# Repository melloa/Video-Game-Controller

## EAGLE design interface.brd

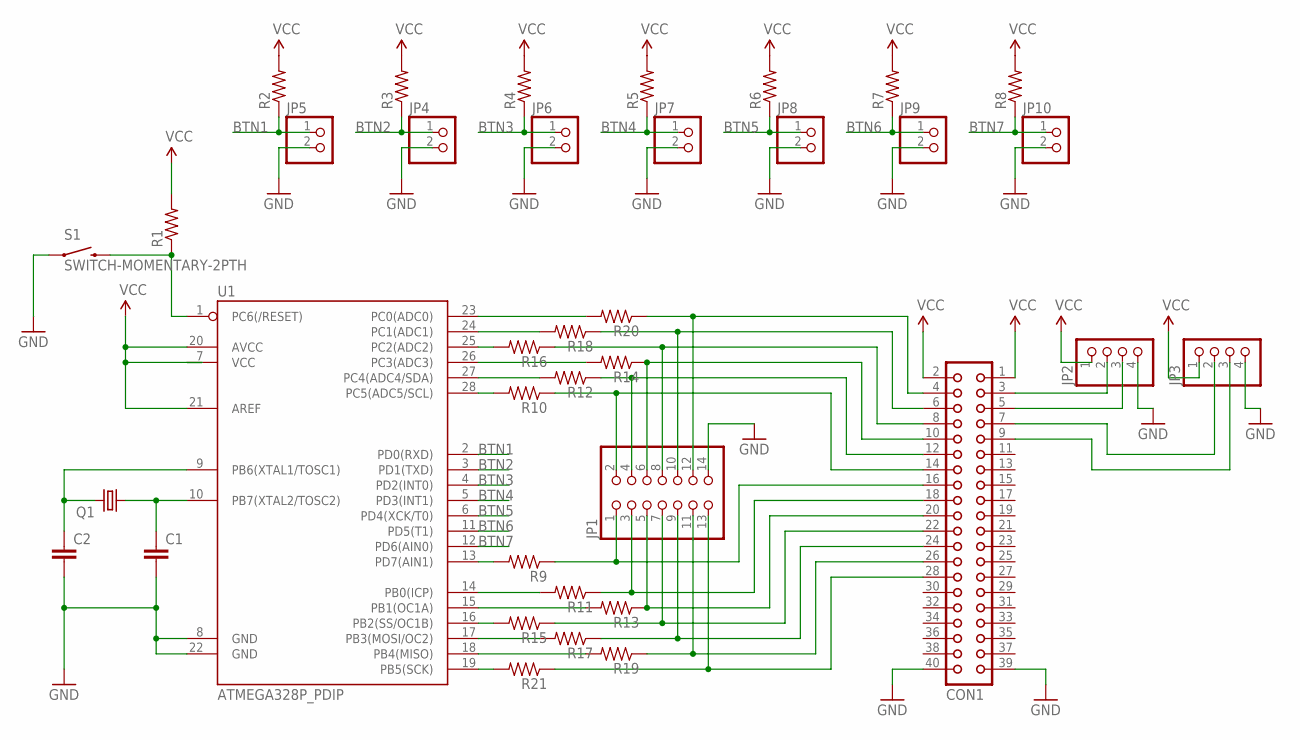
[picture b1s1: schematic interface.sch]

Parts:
C1, C2: CAPPTH; CAP-PTH-SMALL
CON1: CON40
JP1: PINHD-2X7; 2X07
JP2, JP3: PINHD-1X4; 1X04
JP4, JP5, JP6, JP7, JP8, JP9, JP10: PINHD-1X2; 1X02
Q1: CRYSTALHC49S; HC49/S
R1, R2, R3, R4, R5, R6, R7, R8, R9, R10, R11, R12, R13, R14, R15, R16, R17, R18, R19, R20, R21: RESISTORPTH-1/4W; AXIAL-0.4
S1: SWITCH-MOMENTARY-2PTH; TACTILE-PTH
U1: ATMEGA328P_PDIP; DIL28-3

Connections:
BTN1: JP5.1, R2.P$1 (1), U1.2 (PD0(RXD))
BTN2: JP4.1, R3.P$1 (1), U1.3 (PD1(TXD))
BTN3: JP6.1, R4.P$1 (1), U1.4 (PD2(INT0))
BTN4: JP7.1, R5.P$1 (1), U1.5 (PD3(INT1))
BTN5: JP8.1, R6.P$1 (1), U1.6 (PD4(XCK/T0))
BTN6: JP9.1, R7.P$1 (1), U1.11 (PD5(T1))
BTN7: JP10.1, R8.P$1 (1), U1.12 (PD6(AIN0))
GND: C1.2, C2.2, CON1.39, CON1.40, JP1.14, JP2.4, JP3.4, JP4.2, JP5.2, JP6.2, JP7.2, JP8.2, JP9.2, JP10.2, S1.1, U1.8 (GND), U1.22 (GND)
unnamed: C1.1, Q1.1, U1.10 (PB7(XTAL2/TOSC2))
unnamed: C2.1, Q1.2, U1.9 (PB6(XTAL1/TOSC1))
unnamed: R1.P$1 (1), S1.3 (2), U1.1 (PC6(/RESET))
unnamed: R9.P$2 (2), U1.13 (PD7(AIN1))
unnamed: CON1.16, JP1.1, R9.P$1 (1)
unnamed: R11.P$2 (2), U1.14 (PB0(ICP))
unnamed: CON1.18, JP1.3, R11.P$1 (1)
unnamed: CON1.20, JP1.5, R13.P$1 (1)
unnamed: R13.P$2 (2), U1.15 (PB1(OC1A))
unnamed: R15.P$2 (2), U1.16 (PB2(SS/OC1B))
unnamed: CON1.22, JP1.7, R15.P$1 (1)
unnamed: CON1.24, JP1.9, R17.P$1 (1)
unnamed: R17.P$2 (2), U1.17 (PB3(MOSI/OC2))
unnamed: R19.P$2 (2), U1.18 (PB4(MISO))
unnamed: R21.P$2 (2), U1.19 (PB5(SCK))
unnamed: CON1.28, JP1.13, R21.P$1 (1)
unnamed: CON1.7, JP3.2
unnamed: CON1.9, JP3.3
unnamed: CON1.5, JP2.3
unnamed: CON1.3, JP2.2
unnamed: CON1.26, JP1.11, R19.P$1 (1)
unnamed: R10.P$2 (2), U1.28 (PC5(ADC5/SCL))
unnamed: CON1.14, JP1.2, R10.P$1 (1)
unnamed: R12.P$2 (2), U1.27 (PC4(ADC4/SDA))
unnamed: CON1.12, JP1.4, R12.P$1 (1)
unnamed: R14.P$2 (2), U1.26 (PC3(ADC3))
unnamed: CON1.10, JP1.6, R14.P$1 (1)
unnamed: R16.P$2 (2), U1.25 (PC2(ADC2))
unnamed: CON1.8, JP1.8, R16.P$1 (1)
unnamed: R18.P$2 (2), U1.24 (PC1(ADC1))
unnamed: CON1.6, JP1.10, R18.P$1 (1)
unnamed: R20.P$2 (2), U1.23 (PC0(ADC0))
unnamed: CON1.4, JP1.12, R20.P$1 (1)
VCC: CON1.1, CON1.2, JP2.1, JP3.1, R1.P$2 (2), R2.P$2 (2), R3.P$2 (2), R4.P$2 (2), R5.P$2 (2), R6.P$2 (2), R7.P$2 (2), R8.P$2 (2), U1.20 (AVCC), U1.21 (AREF)

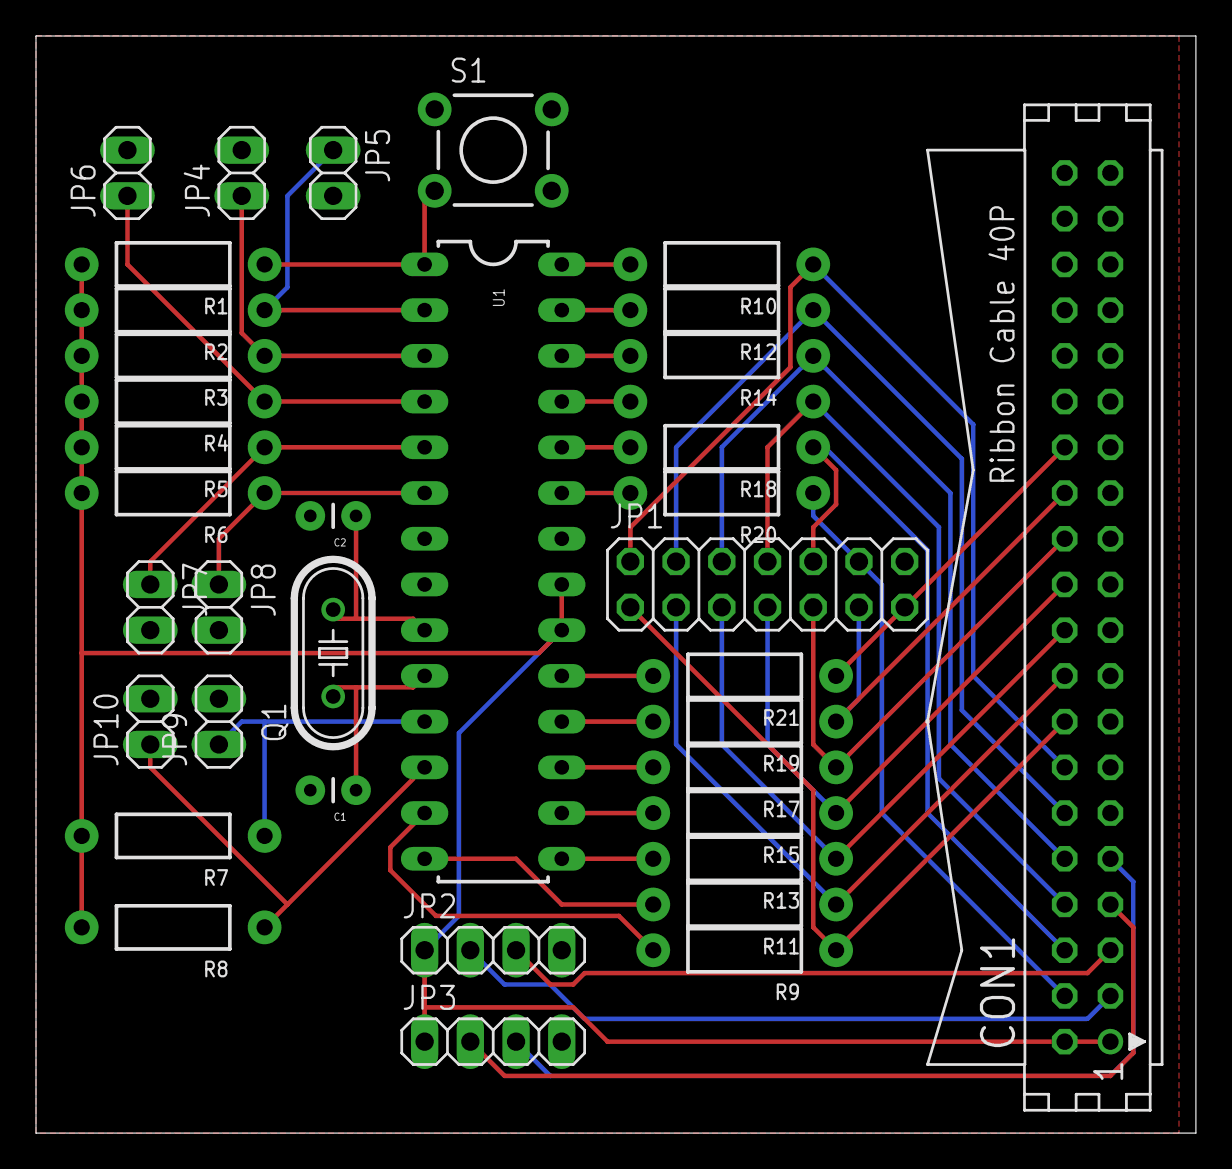
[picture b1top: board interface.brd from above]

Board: 2 copper layers, 64.4 x 61.0 mm, 37 parts (1 on the bottom side), 42 nets.

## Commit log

2016-05-02 :neckbeard: Added .gitattributes & .gitignore files
2016-05-02 Initial Commit
    Empty project
2016-05-02 Started schematic
    ATmega328 should function. No labels. Need to add connectors for buttons
    and resistors to led header
2016-05-02 Add EAGLE temp files to .gitignore
    Added *.s#*, *.b#*, *.l#*
2016-05-06 Rough draft on schematic complete. Checklist of areas to check created
2016-05-06 Add *.lck files
    Ignore EAGLE lock files
2016-05-06 Started layout
2016-05-07 Reorg the schematic. First pass at autorouter
    Need to check if LED resistors will affect XBox circuitry
2016-05-07 Resized, first pass completed

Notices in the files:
parts and their libraries:
SparkFun-Capacitors: Licensing: Creative Commons ShareAlike 4.0 International - https://creativecommons.org/licenses/by-sa/4.0
